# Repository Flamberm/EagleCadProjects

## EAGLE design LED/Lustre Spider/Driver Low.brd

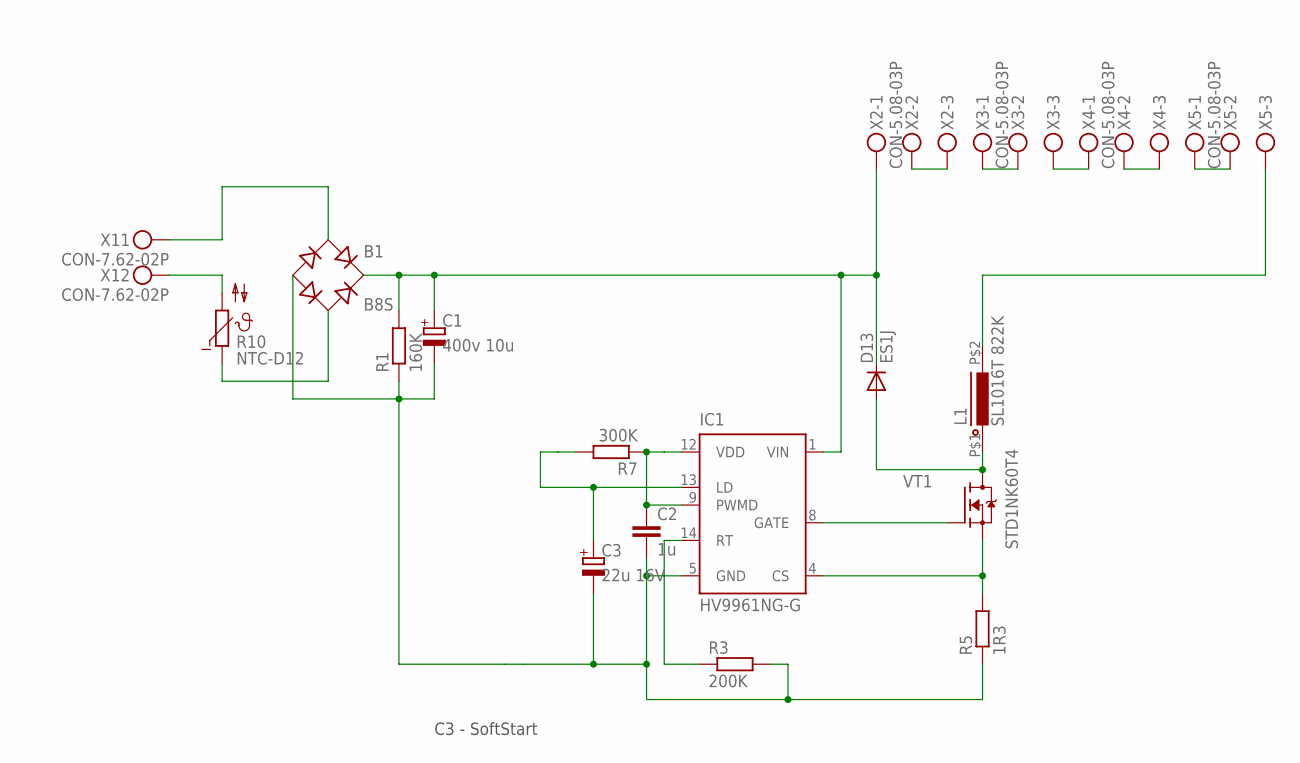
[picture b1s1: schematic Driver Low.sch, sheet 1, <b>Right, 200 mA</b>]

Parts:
B1: B8S; MBS
C1: 400v 10u; E3,5-8
C2: 1u; C0805
C3: 22u 16V; CT3528
D13: ES1J; DO214AC
IC1: HV9961NG-G; SOIC-16NG
L1: SL1016T 822K; SL1016
R1: 160K; MF-0125
R3: 200K; R0805
R5: 1R3; R0805
R7: 300K; R0805
R10: NTC-D12
VT1: STD1NK60T4; DPAK
X1: CON-7.62-02P; KF25C-7.62-02P-13
X2, X3, X4, X5: CON-5.08-03P; MKDSN1,5/3-5,08

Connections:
unnamed: X2.2, X2.3
unnamed: C3.+, IC1.13 (LD), R7.2
unnamed: C2.1, IC1.9 (PWMD), IC1.12 (VDD), R7.1
unnamed: X3.1, X3.2
unnamed: X3.3, X4.1
unnamed: X4.2, X4.3
unnamed: X5.1, X5.2
unnamed: B1.AC1, X1.P$1
unnamed: B1.AC2, R10.1
unnamed: B1.-, C1.-, C2.2, C3.-, IC1.5 (GND), R1.1, R3.2, R5.1
unnamed: B1.+, C1.+, D13.C, IC1.1 (VIN), R1.2, X2.1
unnamed: IC1.4 (CS), R5.2, VT1.S
unnamed: IC1.14 (RT), R3.1
unnamed: IC1.8 (GATE), VT1.G
unnamed: L1.P$2 (2), X5.3
unnamed: D13.A, L1.P$1 (1), VT1.D
unnamed: R10.2, X1.P$2

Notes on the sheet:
C3 - SoftStart

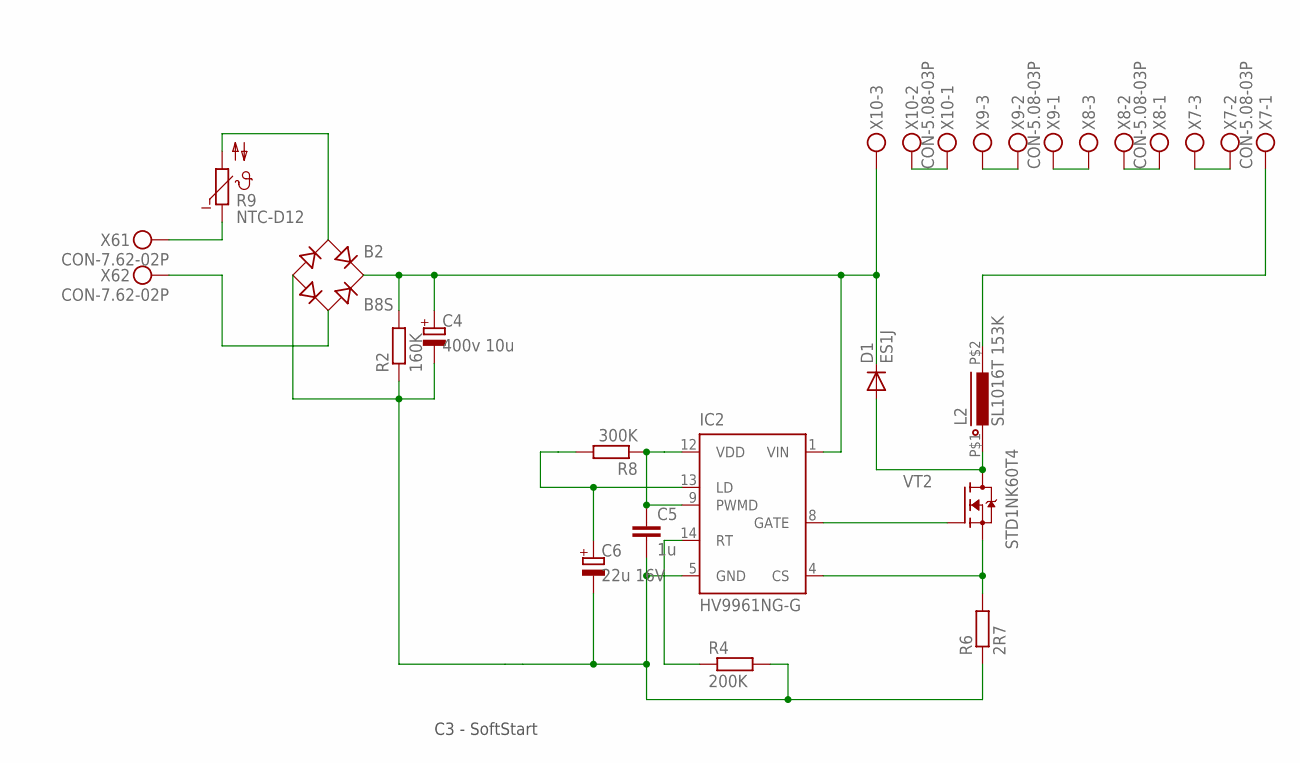
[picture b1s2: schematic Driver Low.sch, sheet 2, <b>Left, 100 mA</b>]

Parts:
B2: B8S; MBS
C4: 400v 10u; E3,5-8
C5: 1u; C0805
C6: 22u 16V; CT3528
D1: ES1J; DO214AC
IC2: HV9961NG-G; SOIC-16NG
L2: SL1016T 153K; SL1016
R2: 160K; MF-0125
R4: 200K; R0805
R6: 2R7; R0805
R8: 300K; R0805
R9: NTC-D12
VT2: STD1NK60T4; DPAK
X6: CON-7.62-02P; KF25C-7.62-02P-13
X7, X8, X9, X10: CON-5.08-03P; MKDSN1,5/3-5,08

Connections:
unnamed: B2.AC1, R9.2
unnamed: B2.AC2, X6.P$2
unnamed: IC2.14 (RT), R4.1
unnamed: IC2.8 (GATE), VT2.G
unnamed: L2.P$2 (2), X7.1
unnamed: D1.A, L2.P$1 (1), VT2.D
unnamed: IC2.4 (CS), R6.2, VT2.S
unnamed: B2.-, C4.-, C5.2, C6.-, IC2.5 (GND), R2.1, R4.2, R6.1
unnamed: B2.+, C4.+, D1.C, IC2.1 (VIN), R2.2, X10.3
unnamed: C6.+, IC2.13 (LD), R8.2
unnamed: C5.1, IC2.9 (PWMD), IC2.12 (VDD), R8.1
unnamed: X7.2, X7.3
unnamed: X8.1, X8.2
unnamed: X8.3, X9.1
unnamed: X9.2, X9.3
unnamed: X10.1, X10.2
unnamed: R9.1, X6.P$1

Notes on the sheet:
C3 - SoftStart

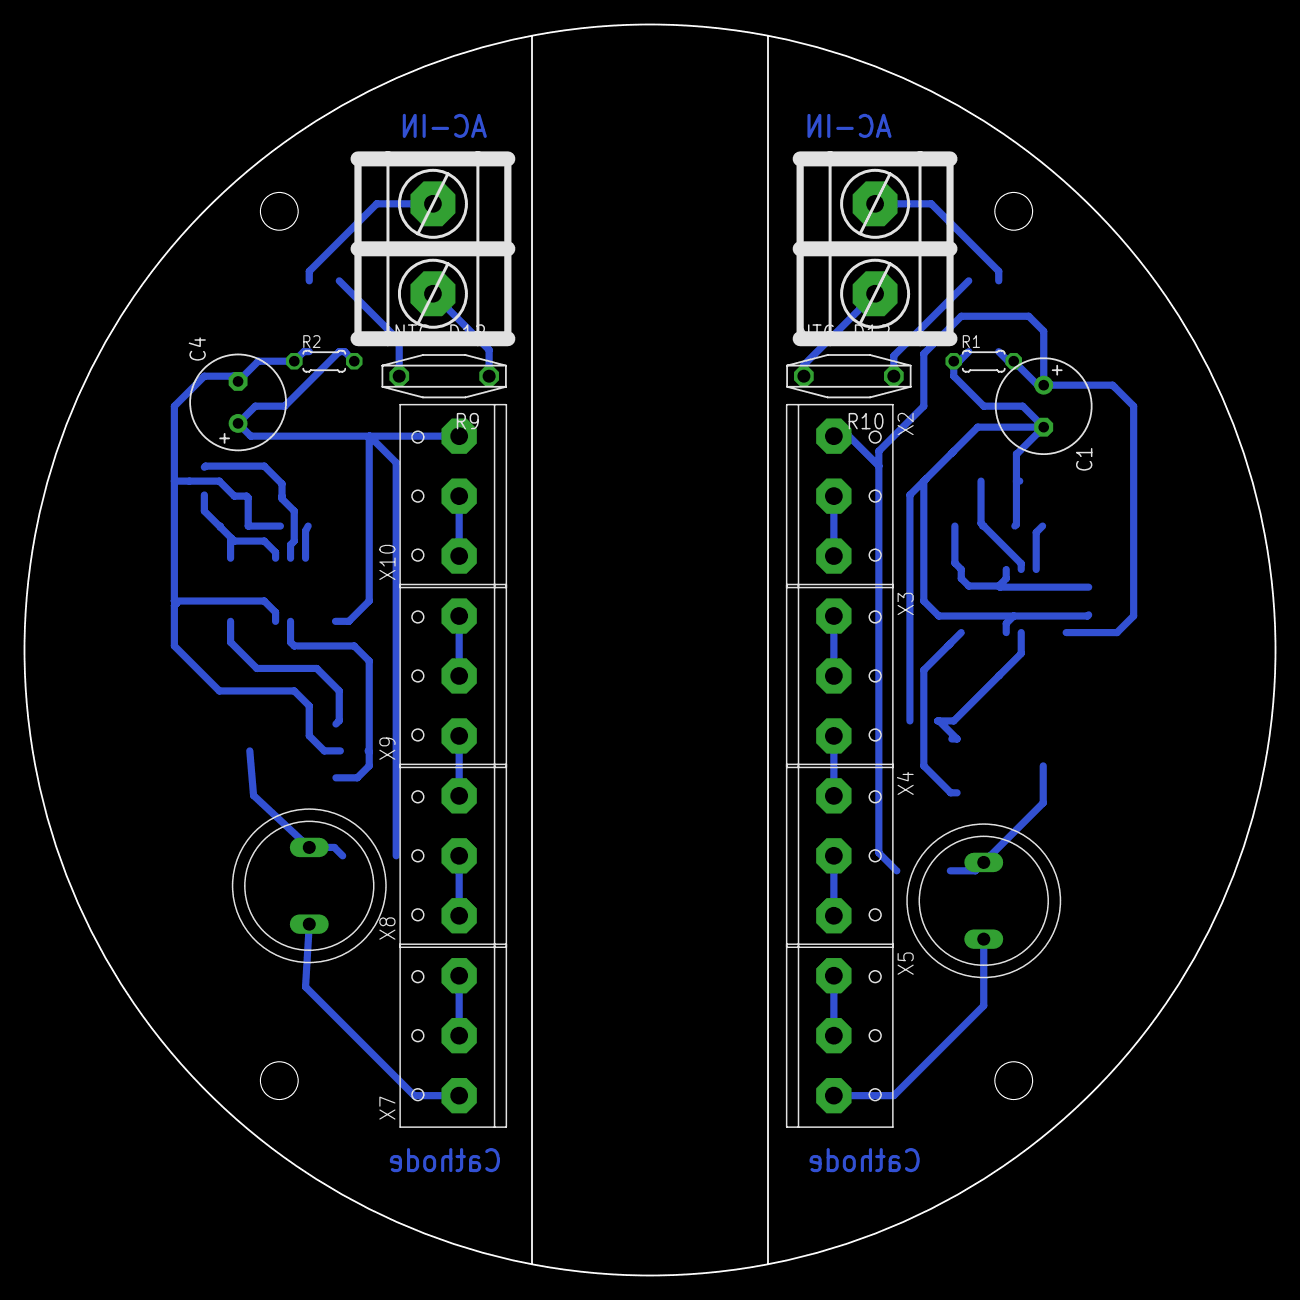
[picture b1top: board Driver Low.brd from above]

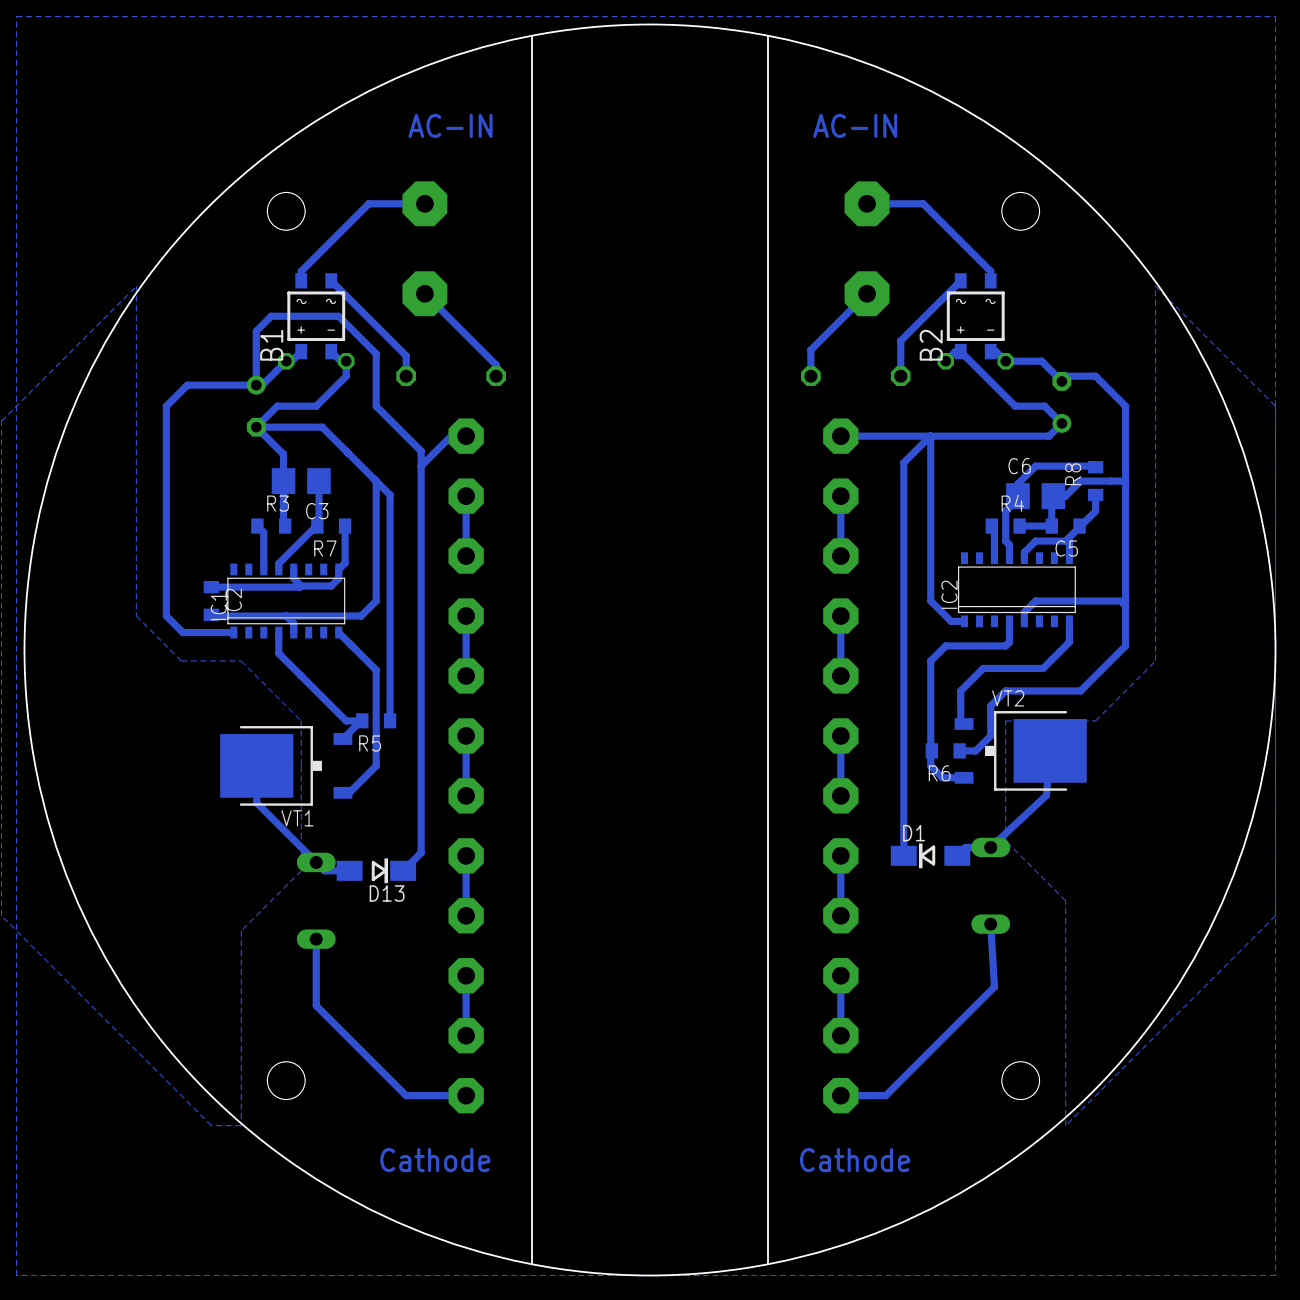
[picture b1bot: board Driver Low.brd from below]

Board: 2 copper layers, 106.0 x 106.0 mm, 36 parts (18 on the bottom side), 34 nets.

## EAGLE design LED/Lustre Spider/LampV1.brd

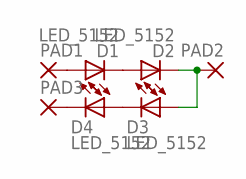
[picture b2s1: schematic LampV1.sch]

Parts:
D1, D2, D3, D4: LED_5152; LED-5152
PAD1, PAD2, PAD3: 2,54/1,1

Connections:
1: D1.A, PAD1.1
2: D1.C, D2.A
3: D2.C, D3.A, PAD2.1
4: D3.C, D4.A
5: D4.C, PAD3.1

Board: 2 copper layers, 7 parts (2 on the bottom side), 5 nets, no tracks yet.

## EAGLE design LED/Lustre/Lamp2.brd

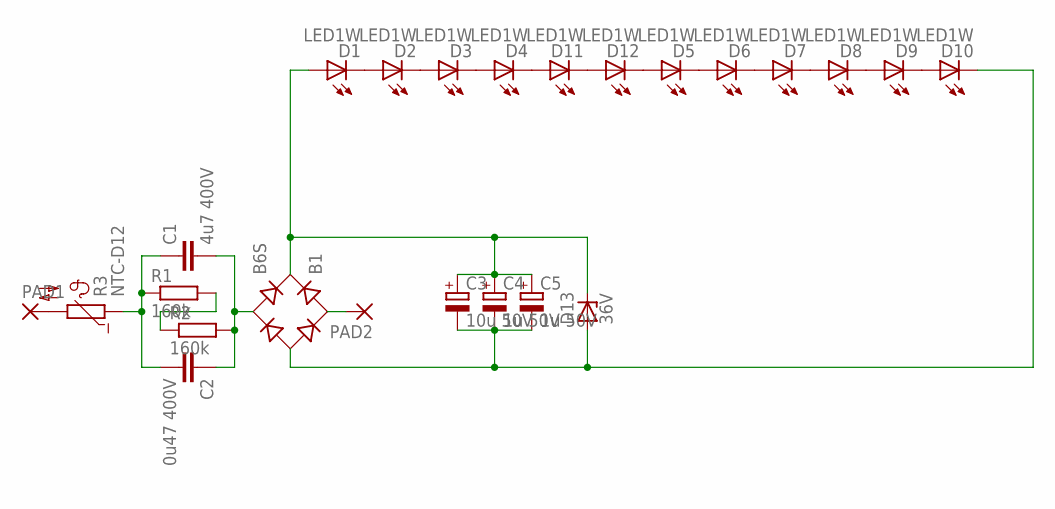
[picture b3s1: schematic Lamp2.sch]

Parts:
B1: B6S; MBS
C1: 4u7 400V; C275-134X316
C2: 0u47 400V; C150-054X183
C3: 10u 50V; E2,5-5
C4, C5: 1u 50V; E2,5-5
D1, D2, D3, D4, D5, D6, D7, D8, D9, D10, D11, D12: LED1W; LED-1W
D13: 36V; ZDIO-5
PAD1, PAD2: 3,81/1,4
R1, R2: 160k; 0204/5
R3: NTC-D12

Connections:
unnamed: D1.K (C), D2.A
unnamed: D2.K (C), D3.A
unnamed: D3.K (C), D4.A
unnamed: D4.K (C), D11.A
unnamed: D5.K (C), D6.A
unnamed: D6.K (C), D7.A
unnamed: D7.K (C), D8.A
unnamed: D8.K (C), D9.A
unnamed: D9.K (C), D10.A
unnamed: C1.1, C2.2, R1.1, R3.1
unnamed: B1.AC1, PAD2.1
unnamed: D11.K (C), D12.A
unnamed: D5.A, D12.K (C)
unnamed: B1.AC2, C1.2, C2.1, R2.2
unnamed: R1.2, R2.1
unnamed: PAD1.1, R3.2
unnamed: B1.+, C3.+, C4.+, C5.+, D1.A, D13.C
unnamed: B1.-, C3.-, C4.-, C5.-, D10.K (C), D13.A

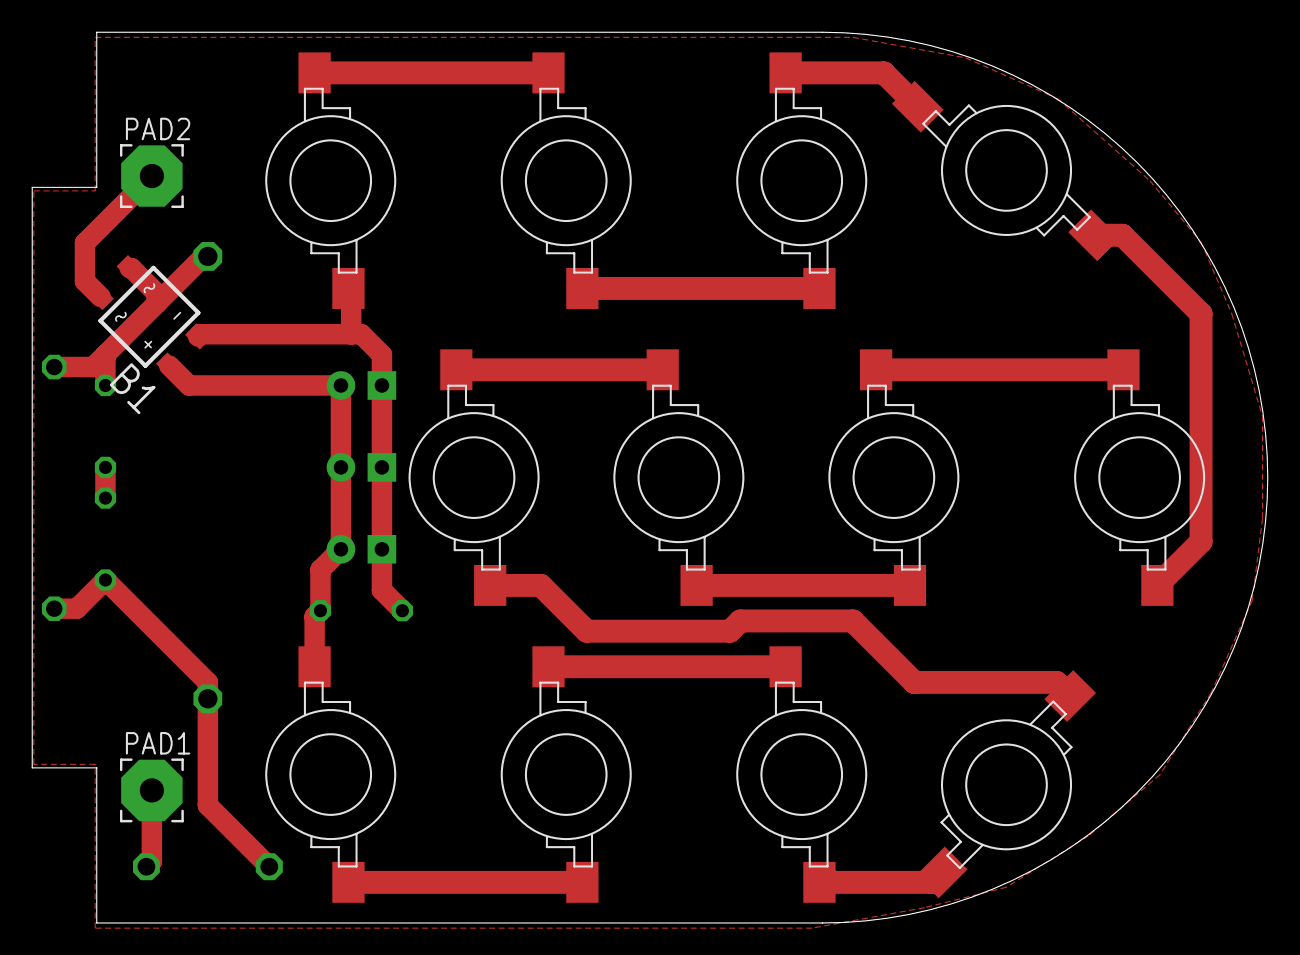
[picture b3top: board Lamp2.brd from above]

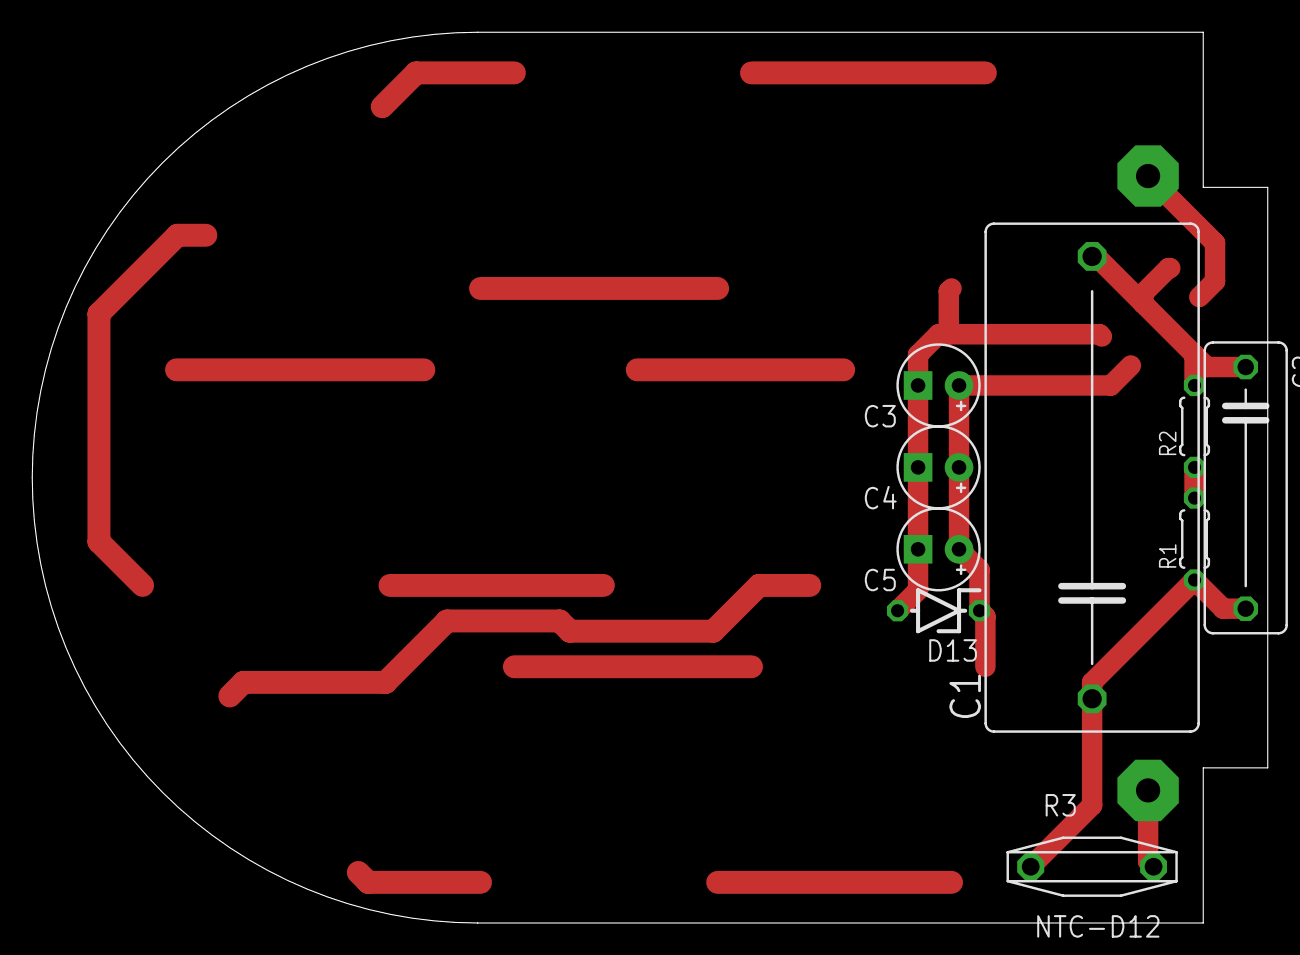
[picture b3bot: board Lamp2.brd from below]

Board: 2 copper layers, 76.6 x 55.2 mm, 24 parts (9 on the bottom side), 18 nets.

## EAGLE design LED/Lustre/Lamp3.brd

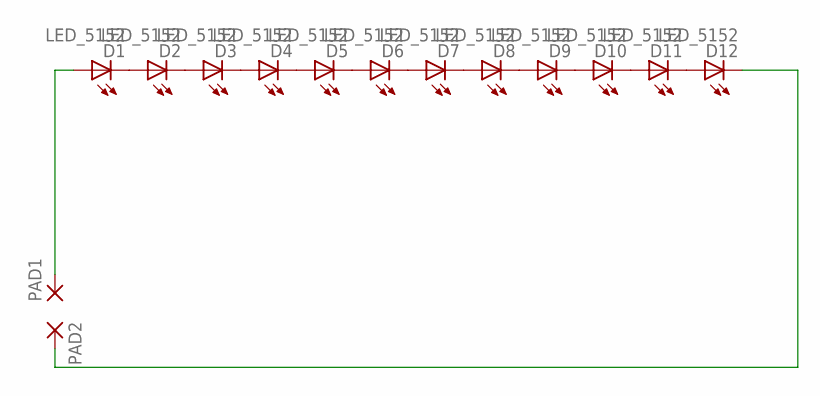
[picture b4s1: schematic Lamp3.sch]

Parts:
D1, D2, D3, D4, D5, D6, D7, D8, D9, D10, D11, D12: LED_5152; LED-5152
PAD1, PAD2: SMD5; SMD2,54-5,08

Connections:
1: D1.A, PAD1.1
2: D1.C, D2.A
3: D2.C, D3.A
4: D3.C, D4.A
5: D4.C, D5.A
6: D5.C, D6.A
7: D6.C, D7.A
8: D7.C, D8.A
9: D8.C, D9.A
10: D9.C, D10.A
11: D10.C, D11.A
12: D11.C, D12.A
13: D12.C, PAD2.1

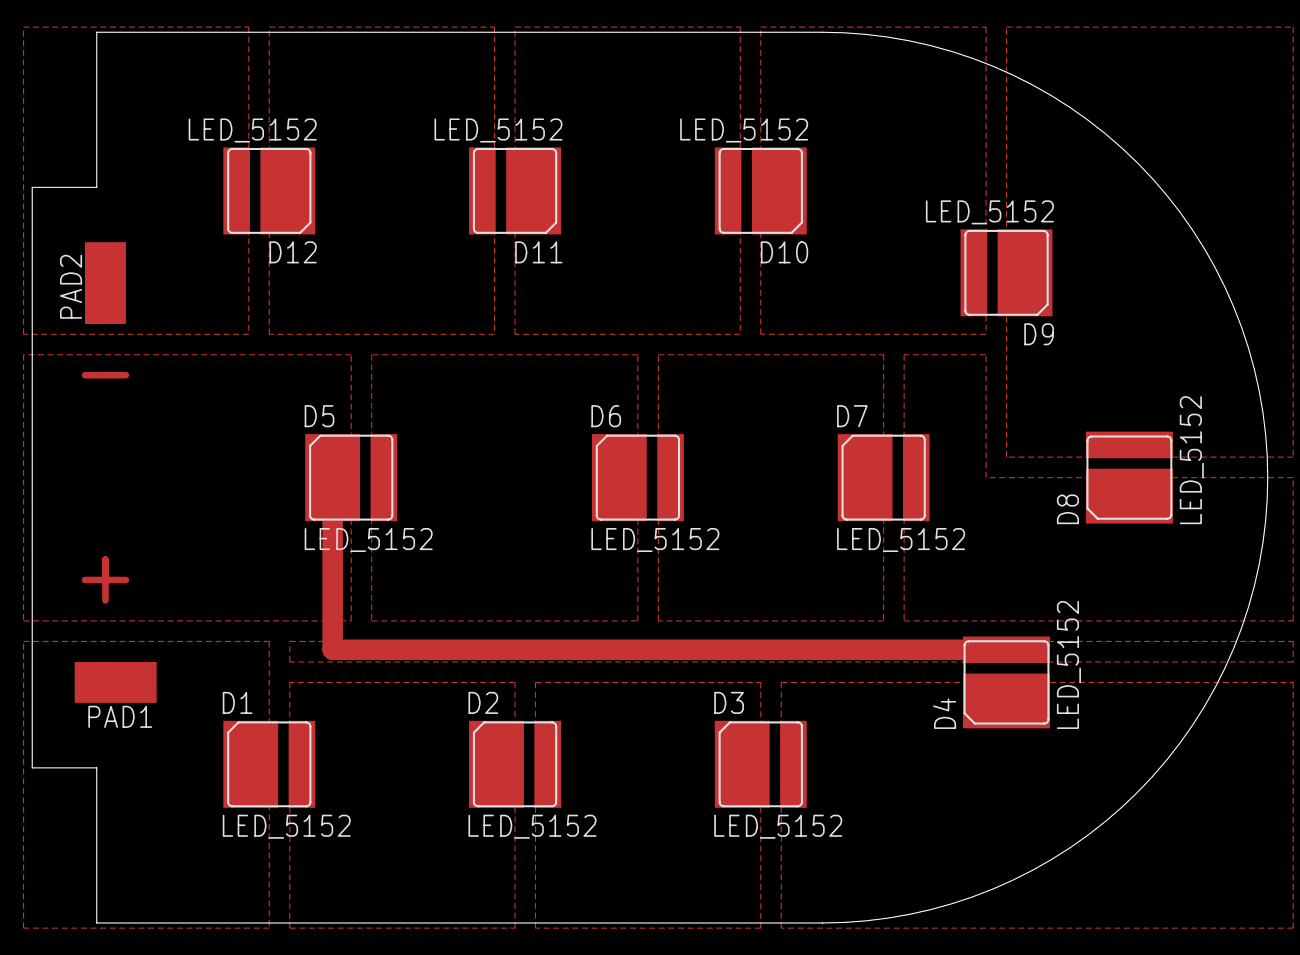
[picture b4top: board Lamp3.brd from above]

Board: 2 copper layers, 76.6 x 55.2 mm, 14 parts (0 on the bottom side), 13 nets.

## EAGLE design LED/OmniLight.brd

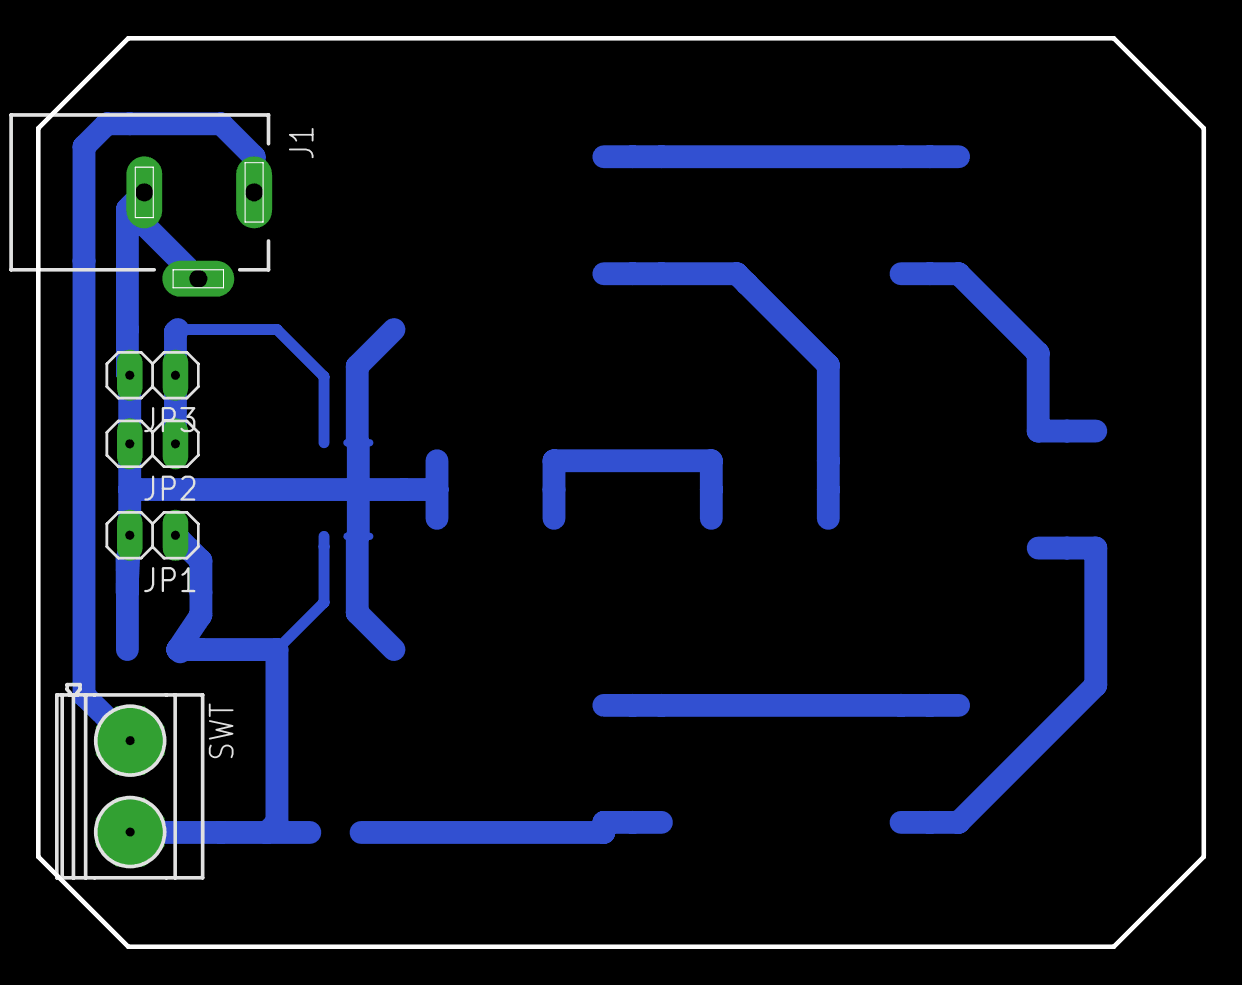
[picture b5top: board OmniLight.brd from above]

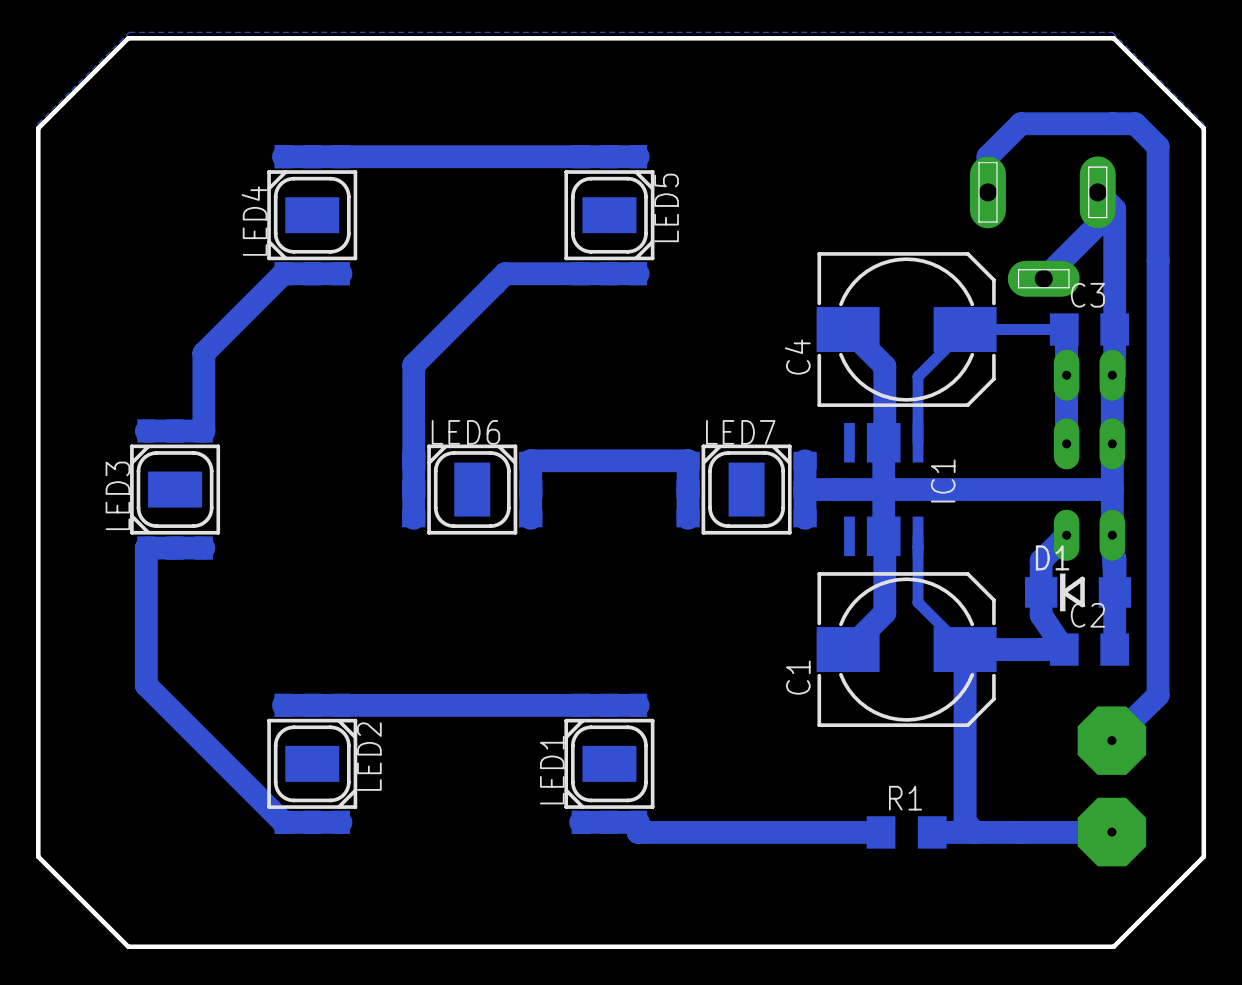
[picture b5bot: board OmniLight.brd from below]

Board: 2 copper layers, 64.8 x 50.5 mm, 19 parts (14 on the bottom side), 12 nets.

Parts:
C1, C4: 140CLH-0810
C2, C3: 330n; C1206
D1: DO214AC
IC1: 78L05SMD; SO08
J1: DCJ0202
JP1: Motor; 1X02
JP2: Line1; 1X02
JP3: Line2; 1X02
LED1, LED2, LED3, LED4, LED5, LED6, LED7: LP2C63-ST-RGB-SR0
R1: 27R; R1206
SWT: MKDSN1,5/2-5,08

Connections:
GND: LED1.TH, LED2.TH, LED3.TH, LED4.TH, LED5.TH, LED6.TH, LED7.TH
unnamed: LED1.1, LED1.2, LED1.3, R1.1
unnamed: LED1.4, LED1.5, LED1.6, LED2.1, LED2.2, LED2.3
unnamed: J1.1, SWT.1
unnamed: C1.+, C2.1, D1.C, IC1.8, JP1.1, R1.2, SWT.2
unnamed: LED2.4, LED2.5, LED2.6, LED3.1, LED3.2, LED3.3
unnamed: LED3.4, LED3.5, LED3.6, LED4.1, LED4.2, LED4.3
unnamed: C1.-, C2.2, C3.2, C4.-, D1.A, IC1.2, IC1.3, IC1.6, IC1.7, J1.2, J1.3, JP1.2, JP2.2, JP3.2, LED7.4, LED7.5, LED7.6
unnamed: LED4.4, LED4.5, LED4.6, LED5.1, LED5.2, LED5.3
unnamed: LED5.4, LED5.5, LED5.6, LED6.1, LED6.2, LED6.3
unnamed: LED6.4, LED6.5, LED6.6, LED7.1, LED7.2, LED7.3
unnamed: C3.1, C4.+, IC1.1, JP2.1, JP3.1

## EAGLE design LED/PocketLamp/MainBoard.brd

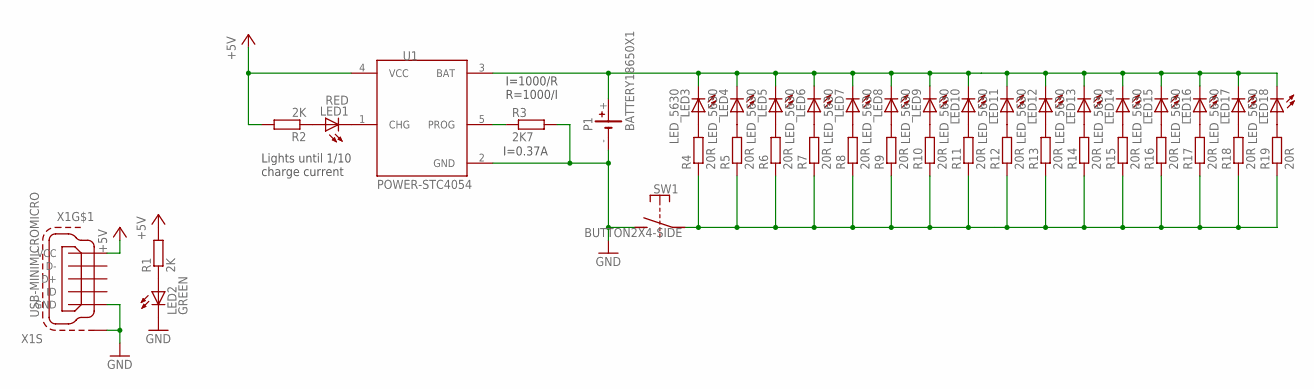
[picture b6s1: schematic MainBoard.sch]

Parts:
LED1: RED; LED1206
LED2: GREEN; LED1206
LED3, LED4, LED5, LED6, LED7, LED8, LED9, LED10, LED11, LED12, LED13, LED14, LED15, LED16, LED17, LED18: LED_5630; LED5730
P1: BATTERY18650X1; 18650X1_HOLDER
R1, R2: 2K; RESC2012X50
R3: 2K7; RESC2012X50
R4, R5, R6, R7, R8, R9, R10, R11, R12, R13, R14, R15, R16, R17, R18, R19: 20R; RESC2012X50
SW1: BUTTON2X4-SIDE; SW-2X4-SIDE
U1: POWER-STC4054; SOT95P280X145-5
X1: USB-MINIMICROMICRO; USB-B-MICRO-SMD

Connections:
+5V: R1.2, R2.2, U1.4 (VCC), X1.VBUS (VCC)
GND: LED2.C, P1.-, R3.2, SW1.2, U1.2 (GND), X1.GND, X1.SHIELD1 (S1), X1.SHIELD2 (S1), X1.SHIELD3 (S1)
unnamed: LED1.C, U1.1 (CHG)
unnamed: LED1.A, R2.1
unnamed: LED2.A, R1.1
unnamed: LED3.C, LED4.C, LED5.C, LED6.C, LED7.C, LED8.C, LED9.C, LED10.C, LED11.C, LED12.C, LED13.C, LED14.C, LED15.C, LED16.C, LED17.C, LED18.C, P1.+, U1.3 (BAT)
unnamed: R3.1, U1.5 (PROG)
unnamed: LED3.A, LED3.A1 (A), R4.2
unnamed: R4.1, R5.1, R6.1, R7.1, R8.1, R9.1, R10.1, R11.1, R12.1, R13.1, R14.1, R15.1, R16.1, R17.1, R18.1, R19.1, SW1.1
unnamed: LED4.A, LED4.A1 (A), R5.2
unnamed: LED11.A, LED11.A1 (A), R12.2
unnamed: LED5.A, LED5.A1 (A), R6.2
unnamed: LED12.A, LED12.A1 (A), R13.2
unnamed: LED13.A, LED13.A1 (A), R14.2
unnamed: LED6.A, LED6.A1 (A), R7.2
unnamed: LED14.A, LED14.A1 (A), R15.2
unnamed: LED15.A, LED15.A1 (A), R16.2
unnamed: LED7.A, LED7.A1 (A), R8.2
unnamed: LED16.A, LED16.A1 (A), R17.2
unnamed: LED17.A, LED17.A1 (A), R18.2
unnamed: LED8.A, LED8.A1 (A), R9.2
unnamed: LED18.A, LED18.A1 (A), R19.2
unnamed: LED9.A, LED9.A1 (A), R10.2
unnamed: LED10.A, LED10.A1 (A), R11.2

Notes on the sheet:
I=1000/R R=1000/I
I=0.37A
Lights until 1/10 charge current

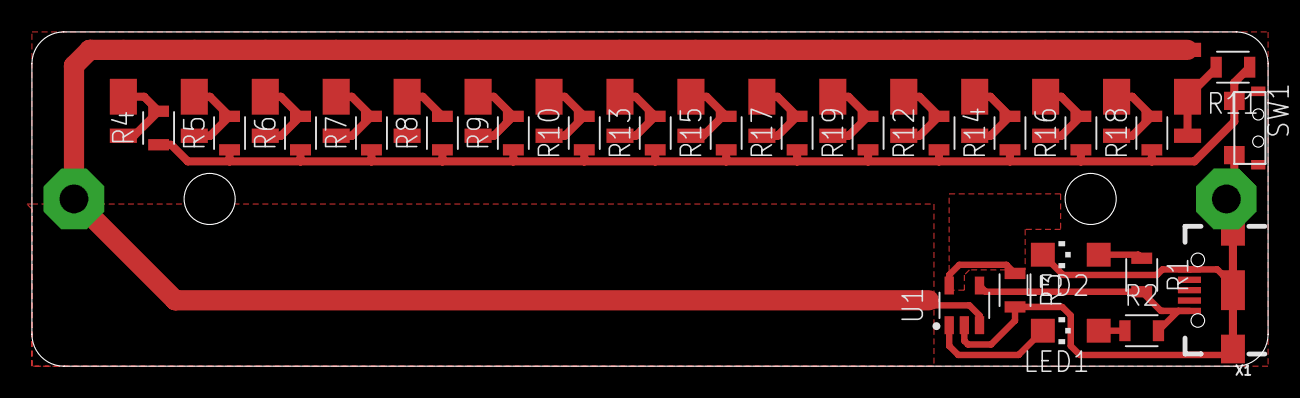
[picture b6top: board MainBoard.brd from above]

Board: 2 copper layers, 77.5 x 20.9 mm, 41 parts (1 on the bottom side), 24 nets.
